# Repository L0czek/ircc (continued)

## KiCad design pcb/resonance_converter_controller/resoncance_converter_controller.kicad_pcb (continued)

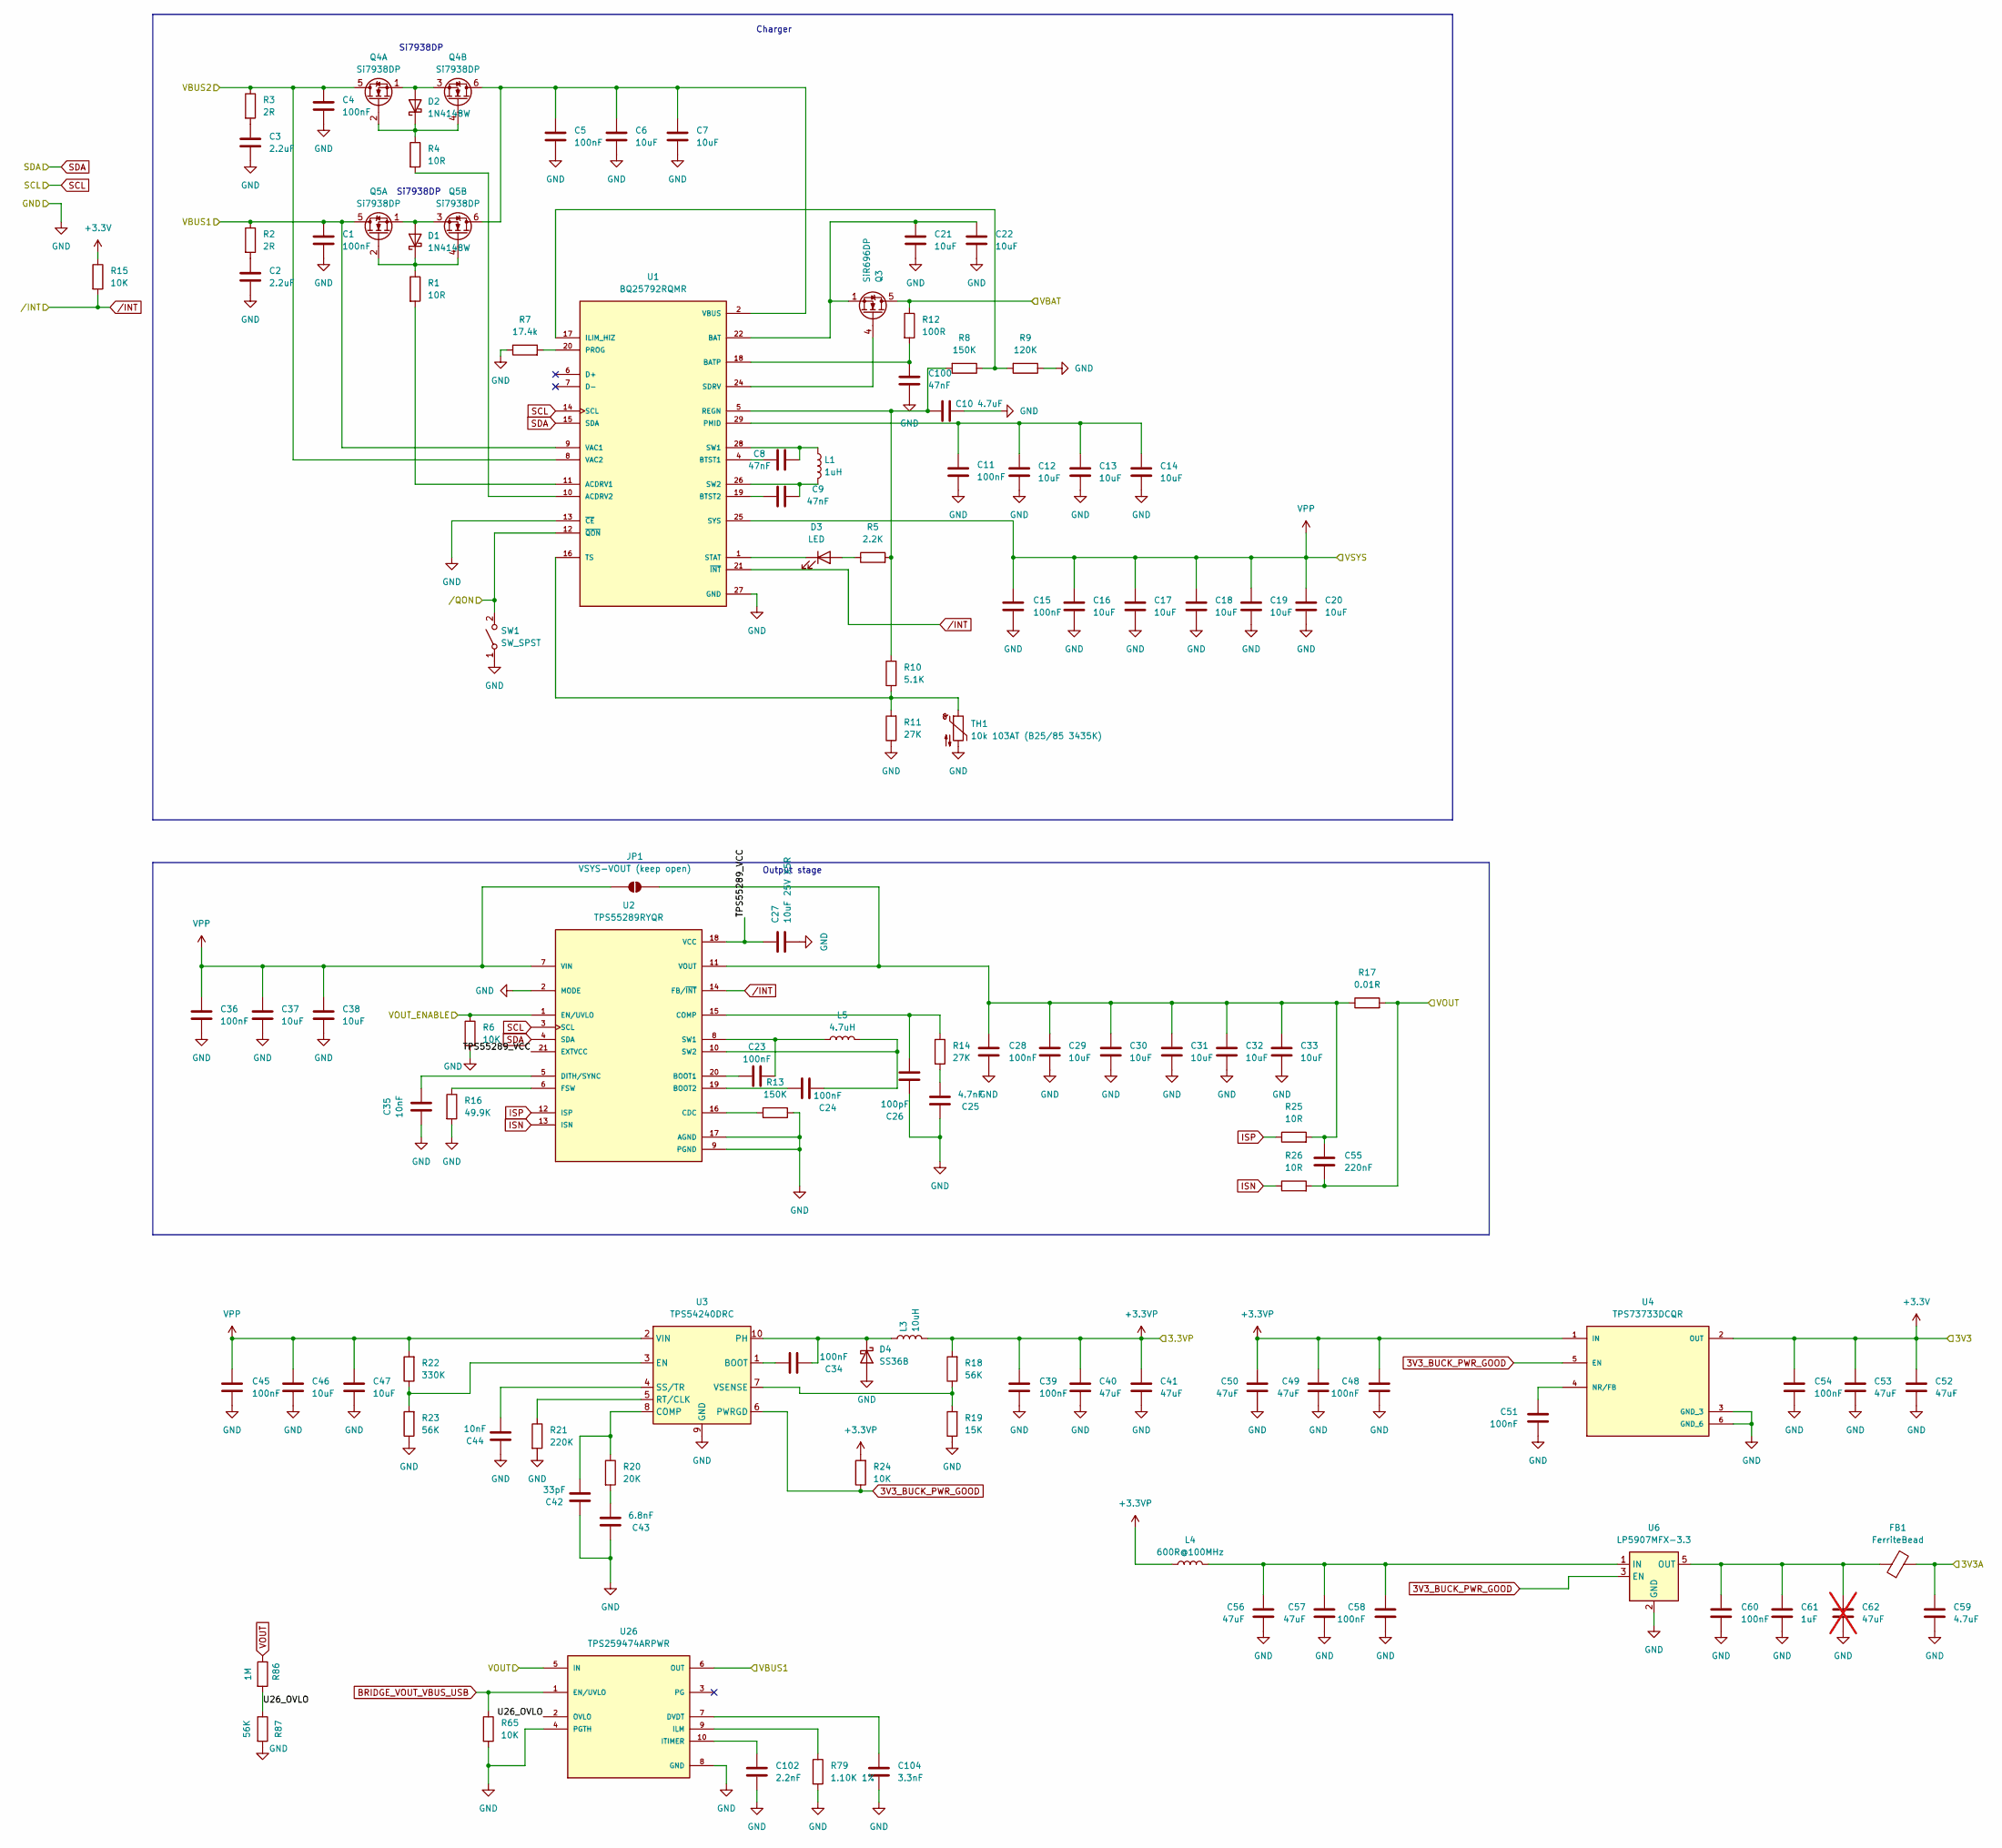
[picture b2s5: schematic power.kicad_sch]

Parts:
C1, C4, C5, C11, C15, C23, C24, C28, C34, C36, C39, C45, C48, C51, C54, C58, C60: 100nF; C_0402_1005Metric; LCSC C307331
C2, C3: 2.2uF; C_1206_3216Metric; LCSC C50254
C6, C7, C12, C13, C14, C16, C17, C18, C19, C20, C21, C22, C29, C30, C31, C32, C33, C37, C38, C46, C47: 10uF; C_1206_3216Metric; LCSC C13585
C8, C9, C100: 47nF; C_0402_1005Metric
C10: 4.7uF; C_1206_3216Metric; LCSC C29823
C25: 4.7nF; C_0402_1005Metric; LCSC C1538
C26: 100pF; C_0402_1005Metric; LCSC C1546
C27: 10uF 25V X5R; C_0805_2012Metric; LCSC C15850
C35, C44: 10nF; C_0402_1005Metric; LCSC C15195
C40, C41, C49, C50, C52, C53, C56, C57: 47uF; C_1206_3216Metric; LCSC C96123
C42: 33pF; C_0402_1005Metric; LCSC C1562
C43: 6.8nF; C_0402_1005Metric; LCSC C1542
C55: 220nF; C_0402_1005Metric; LCSC C16772
C59: 4.7uF; C_0805_2012Metric; LCSC C1779
C61: 1uF; C_0603_1608Metric; LCSC C15849
C62: 47uF; C_1206_3216Metric; LCSC C96123; not fitted
C102: 2.2nF; C_0402_1005Metric; LCSC C1531
C104: 3.3nF; C_0402_1005Metric; LCSC C26404
D1, D2: 1N4148W; D_SOD-123; LCSC C81598
D3: LED; LED_0805_2012Metric; LCSC C84256
D4: SS36B; D_SMB; LCSC C18199182
FB1: FerriteBead; L_0805_2012Metric; LCSC C1017
JP1: VSYS-VOUT (keep open); SolderJumper-2_P1.3mm_Open_RoundedPad1.0x1.5mm
L1: 1uH; L_10.4x10.4_H4.8
L3: 10uH; C_2220_5750Metric
L4: 600R@100MHz; L_0805_2012Metric; MPN GZ2012D601TF; LCSC C1017
L5: 4.7uH; MPEV1D1040L4R7; MPN MPEV1D1040L4R7
Q3: SiR696DP; PowerPAK_SO-8_Single
Q4, Q5: Si7938DP; PowerPAK_SO-8_Dual
R1, R4, R25, R26: 10R; R_0402_1005Metric; LCSC C25077
R2, R3: 2R; R_1206_3216Metric; LCSC C137316
R5: 2.2K; R_0402_1005Metric; LCSC C25879
R6, R15, R24, R65: 10K; R_0402_1005Metric; LCSC C25744
R7: 17.4k; R_0402_1005Metric; LCSC C26957
R8, R13: 150K; R_0402_1005Metric; LCSC C25755
R9: 120K; R_0402_1005Metric; LCSC C25750
R10: 5.1K; R_0402_1005Metric; LCSC C25905
R11, R14: 27K; R_0402_1005Metric; LCSC C25771
R12: 100R; R_0402_1005Metric; LCSC C25076
R16: 49.9K; R_0402_1005Metric; LCSC C25897
R17: 0.01R; R_1206_3216Metric; LCSC C188070
R18, R23, R87: 56K; R_0402_1005Metric; LCSC C25796
R19: 15K; R_0402_1005Metric; LCSC C25756
R20: 20K; R_0402_1005Metric; LCSC C25765
R21: 220K; R_0402_1005Metric; LCSC C25767
R22: 330K; R_0402_1005Metric; LCSC C25778
R79: 1.10K 1%; R_0402_1005Metric; LCSC C25860
R86: 1M; R_0402_1005Metric; LCSC C26083
SW1: SW_SPST; SW_SPST_EVQPE1
TH1: 10k 103AT (B25/85 3435K); R_0603_1608Metric; MPN NCP18XH103F03RB; LCSC C13564
U1: BQ25792RQMR; QFN40P400X400X100-29N; PARTREV 11/2019
U2: TPS55289RYQR; VREG_TPS55289RYQR; PARTREV August 2022
U3: TPS54240DRC; Texas_DRC0010J_ThermalVias
U4: TPS73733DCQR; IC_TPS73733DCQR; PARTREV R
U6: LP5907MFX-3.3; SOT-23-5
U26: TPS259474ARPWR; IC_TPS259474ARPWR; PARTREV A

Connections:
3V3_BUCK_PWR_GOOD: R24.1, U3.6 (PWRGD), U4.5 (EN), U6.3 (EN)
+3.3VP: C39.1, C40.1, C41.1, C48.1, C49.1, C50.1, L3.2, L4.1, R18.2, R24.2, U4.1 (IN); also elsewhere on the board
+BATT: Q3.5 (D), R12.1; also elsewhere on the board
/Controller/VOUT_ENABLE: R6.1, U2.1 (EN/UVLO); also elsewhere on the board
/Power supply/TPS55289_VCC: C27.1, U2.18 (VCC), U2.21 (EXTVCC)
/Power supply/U26_OVLO: R86.2, R87.1, U26.2 (OVLO)
BAT: C21.1, C22.1, Q3.1 (S), Q3.2 (S), Q3.3 (S), U1.22 (BAT), U1.23 (BAT)
BRIDGE_VOUT_VBUS_USB: R65.1, U26.1 (EN/UVLO); also elsewhere on the board
GND: C1.2, C2.2, C3.2, C4.2, C5.2, C6.2, C7.2, C10.2, C11.2, C12.2, C13.2, C14.2, C15.2, C16.2, C17.2, C18.2, C19.2, C20.2, C21.2, C22.2, C25.1, C26.1, C27.2, C28.2, C29.2, C30.2, C31.2, C32.2, C33.2, C35.1, C36.2, C37.2, C38.2, C39.2, C40.2, C41.2, C42.1, C43.1, C44.1, C45.2, C46.2, C47.2, C48.2, C49.2, C50.2, C51.2, C52.2, C53.2, C54.2, C56.2, C57.2, C58.2, C59.2, C60.2, C61.2, C62.2, C100.2, C102.2, C104.2, D4.2 (A), R6.2, R7.1, R9.1, R11.1, R13.1, R16.2, R19.1, R21.2, R23.1, R65.2, R79.2, R87.2, SW1.1 (A), TH1.2, U1.13 (~CE), U1.27 (GND), U2.2 (MODE), U2.9 (PGND), U2.17 (AGND), U3.9 (GND), U3.11 (GND), U4.3 (GND_3), U4.6 (GND_6), U6.2 (GND), U26.4 (PGTH), U26.8 (GND); also elsewhere on the board
INT_I2C_SCL: U1.14 (SCL), U2.3 (SCL); also elsewhere on the board
INT_I2C_SDA: U1.15 (SDA), U2.4 (SDA); also elsewhere on the board
ISN: R26.1, U2.13 (ISN)
ISP: R25.1, U2.12 (ISP)
unnamed: C2.1, R2.2
unnamed: C3.1, R3.2
unnamed: C25.2, R14.2
unnamed: C43.2, R20.2
unnamed: D1.2 (A), Q5.1 (S1), Q5.3 (S2)
unnamed: D1.1 (K), Q5.2 (G1), Q5.4 (G2), R1.1
unnamed: D2.2 (A), Q4.1 (S1), Q4.3 (S2)
unnamed: D2.1 (K), Q4.2 (G1), Q4.4 (G2), R4.1
unnamed: D3.2 (A), R5.1
unnamed: D3.1 (K), U1.1 (STAT)
unnamed: C34.1, D4.1 (K), L3.1, U3.10 (PH)
unnamed: C28.1, C29.1, C30.1, C31.1, C32.1, C33.1, C55.1, JP1.2 (B), R17.1, R25.2, U2.11 (VOUT)
unnamed: Q3.4 (G), U1.24 (SDRV)
unnamed: R1.2, U1.11 (ACDRV1)
unnamed: R4.2, U1.10 (ACDRV2)
unnamed: C100.1, R12.2, U1.18 (BATP)
unnamed: C8.1, U1.4 (BTST1)
unnamed: C9.1, U1.19 (BTST2)
unnamed: R8.1, R9.2, U1.17 (ILIM_HIZ)
unnamed: C11.1, C12.1, C13.1, C14.1, U1.29 (PMID)
unnamed: R7.2, U1.20 (PROG)
unnamed: C10.1, R5.2, R8.2, R10.2, U1.5 (REGN)
unnamed: C8.2, L1.1, U1.28 (SW1)
unnamed: C9.2, L1.2, U1.26 (SW2)
unnamed: R10.1, R11.2, TH1.1, U1.16 (TS)
unnamed: C23.1, U2.20 (BOOT1)
unnamed: C24.2, U2.19 (BOOT2)
unnamed: R13.2, U2.16 (CDC)
unnamed: C26.2, R14.1, U2.15 (COMP)
unnamed: C35.2, U2.5 (DITH/SYNC)
unnamed: R16.1, U2.6 (FSW)
unnamed: C23.2, L5.1, U2.8 (SW1)
unnamed: C24.1, L5.2, U2.10 (SW2)
unnamed: C34.2, U3.1 (BOOT)
unnamed: C42.2, R20.1, U3.8 (COMP)
unnamed: R22.1, R23.2, U3.3 (EN)
unnamed: R21.1, U3.5 (RT/CLK)
unnamed: C44.2, U3.4 (SS/TR)
unnamed: R18.1, R19.2, U3.7 (VSENSE)
unnamed: C51.1, U4.4 (NR/FB)
unnamed: C56.1, C57.1, C58.1, L4.2, U6.1 (IN)
unnamed: C60.1, C61.1, C62.1, FB1.1, U6.5 (OUT)
unnamed: C104.1, U26.7 (DVDT)
unnamed: R79.1, U26.9 (ILM)
unnamed: C102.1, U26.10 (ITIMER)
VAA: C59.1, FB1.2; also elsewhere on the board
VBUS: C5.1, C6.1, C7.1, Q4.6 (D2), Q5.6 (D2), U1.2 (VBUS), U1.3 (VBUS)
VBUS_DOCK: C4.1, Q4.5 (D1), R3.1, U1.8 (VAC2); also elsewhere on the board
VBUS_USBC: C1.1, Q5.5 (D1), R2.1, U1.9 (VAC1), U26.6 (OUT); also elsewhere on the board
VCC: C52.1, C53.1, C54.1, R15.1, U4.2 (OUT); also elsewhere on the board
VOUT: C55.2, R17.2, R26.2, R86.1, U26.5 (IN); also elsewhere on the board
VSYS: C15.1, C16.1, C17.1, C18.1, C19.1, C20.1, C36.1, C37.1, C38.1, C45.1, C46.1, C47.1, JP1.1 (A), R22.2, U1.25 (SYS), U2.7 (VIN), U3.2 (VIN); also elsewhere on the board
/INT: R15.2, U1.21 (~INT), U2.14 (FB/~INT); also elsewhere on the board
/QON: SW1.2 (B), U1.12 (~QON); also elsewhere on the board

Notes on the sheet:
Output stage
Si7938DP
Charger

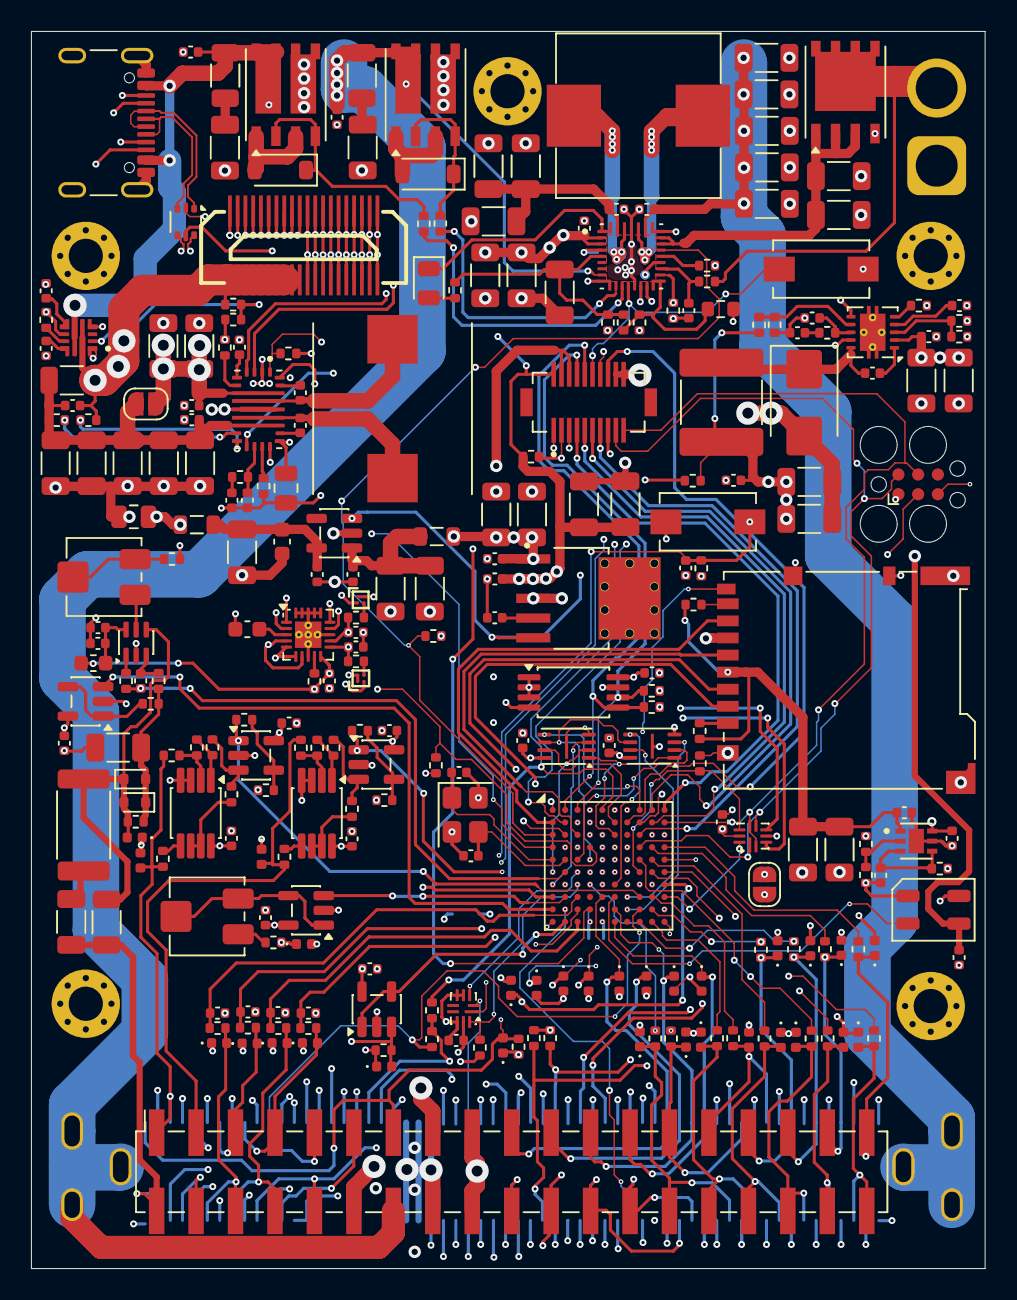
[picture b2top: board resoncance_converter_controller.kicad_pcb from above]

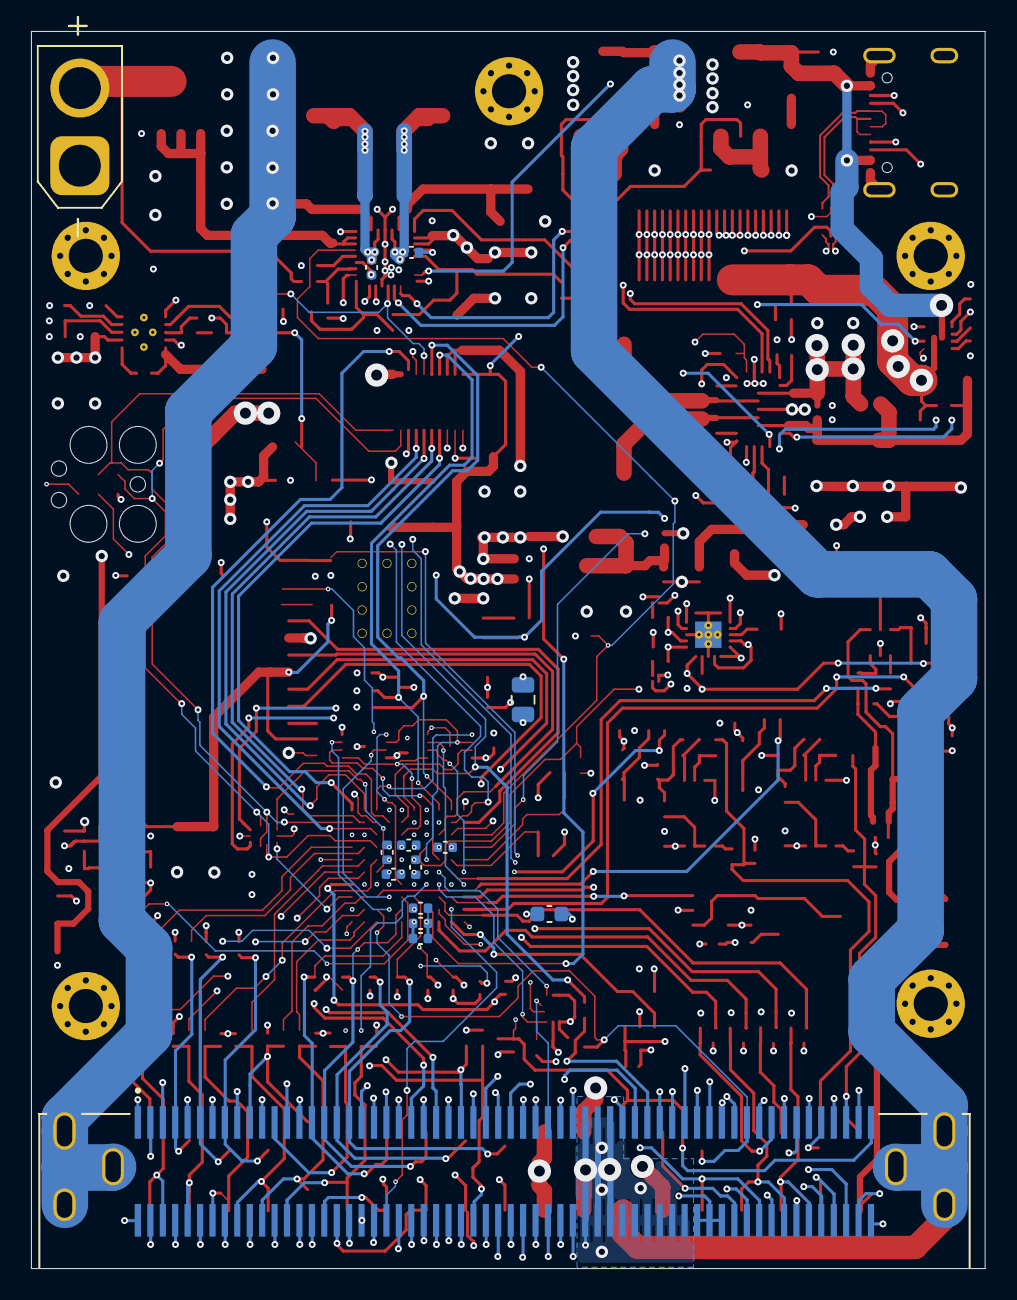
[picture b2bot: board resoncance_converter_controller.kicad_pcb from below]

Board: 6 copper layers, 61.4 x 79.7 mm, 289 parts (14 on the bottom side), 210 nets.

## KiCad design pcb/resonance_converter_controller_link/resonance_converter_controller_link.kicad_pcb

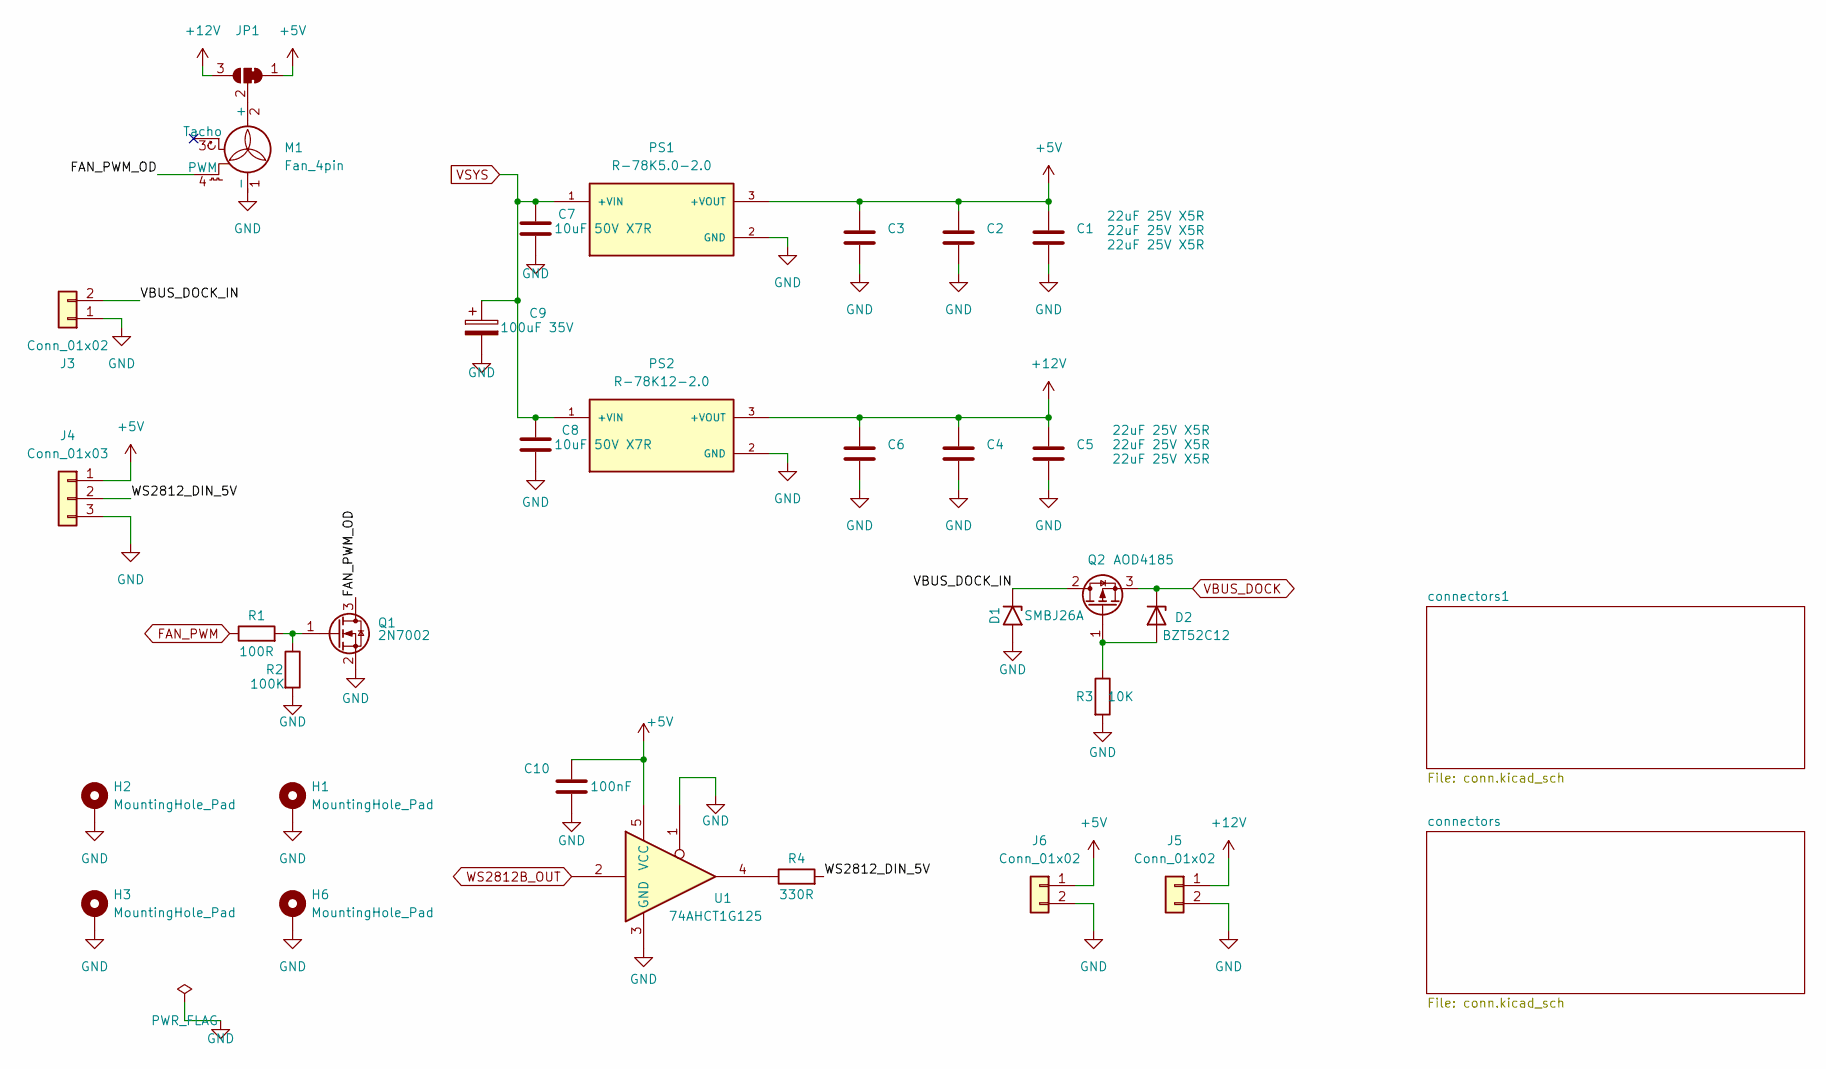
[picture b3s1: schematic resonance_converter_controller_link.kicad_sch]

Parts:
C1, C2, C3, C4, C5, C6: 22uF 25V X5R; C_1206_3216Metric; LCSC Part C12891
C7, C8: 10uF 50V X7R; C_1210_3225Metric
C9: 100uF 35V; CP_Elec_8x10
C10: 100nF; C_0402_1005Metric; LCSC Part C307331
D1: SMBJ26A; D_SMB; MPN SMBJ26A; LCSC Part C19077580
D2: BZT52C12; D_SOD-123; MPN BZT52C12; LCSC Part C19077410
H1, H2, H3, H6: MountingHole_Pad; MountingHole_2.2mm_M2_Pad_Via
J3: Conn_01x02; PhoenixContact_MC_1,5_2-GF-5.08_1x02_P5.08mm_Horizontal_Thr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
J4: Conn_01x03; PinHeader_1x03_P2.54mm_Horizontal
J5, J6: Conn_01x02; PhoenixContact_MC_1,5_2-G-5.08_1x02_P5.08mm_Horizontal
JP1: SolderJumper_3_Bridged12; SolderJumper-3_P1.3mm_Bridged12_RoundedPad1.0x1.5mm
M1: Fan_4pin; FanPinHeader_1x04_P2.54mm_Vertical
PS1: R-78K5.0-2.0; CONV_R-78K5.0-2.0; MPN R-78K5.0-2.0
PS2: R-78K12-2.0; CONV_R-78K12-2.0; MPN R-78K12-2.0
Q1: 2N7002; SOT-23; MPN 2N7002; LCSC Part C8545
Q2: AOD4185; TO-252-2; MPN AOD4185; LCSC Part C400894
R1: 100R; R_0402_1005Metric; LCSC Part C25076
R2: 100K; R_0402_1005Metric; LCSC Part C25741
R3: 10K; R_0402_1005Metric; LCSC Part C25744
R4: 330R; R_0402_1005Metric; LCSC Part C25104
U1: 74AHCT1G125; SOT-23-5; MPN 74AHCT1G125GV; LCSC Part C52140417

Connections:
+5V: C1.1, C2.1, C3.1, C10.1, J4.1, J6.1, JP1.1 (A), PS1.3 (+VOUT), U1.5 (VCC)
+12V: C4.1, C5.1, C6.1, J5.1, JP1.3 (B), PS2.3 (+VOUT)
/FAN_PWM_OD: M1.4 (PWM), Q1.3 (D)
/VBUS_DOCK_IN: D1.1 (A1), J3.2, Q2.2 (D)
/WS2812_DIN_5V: J4.2, R4.2
FAN_PWM: R1.1; also elsewhere on the board
GND: C1.2, C2.2, C3.2, C4.2, C5.2, C6.2, C7.2, C8.2, C9.2, C10.2, D1.2 (A2), H1.1 (1_1), H2.1 (1_1), H3.1 (1_1), H6.1 (1_1), J3.1, J4.3, J5.2, J6.2, M1.1 (-), PS1.2 (GND), PS2.2 (GND), Q1.2 (S), R2.2, R3.2, U1.1, U1.3 (GND); also elsewhere on the board
unnamed: D2.2 (A), Q2.1 (G), R3.1
unnamed: JP1.2 (C), M1.2 (+)
unnamed: Q1.1 (G), R1.2, R2.1
unnamed: R4.1, U1.4
VBUS_DOCK: D2.1 (K), Q2.3 (S); also elsewhere on the board
VSYS: C7.1, C8.1, C9.1, PS1.1 (+VIN), PS2.1 (+VIN); also elsewhere on the board
WS2812B_OUT: U1.2; also elsewhere on the board

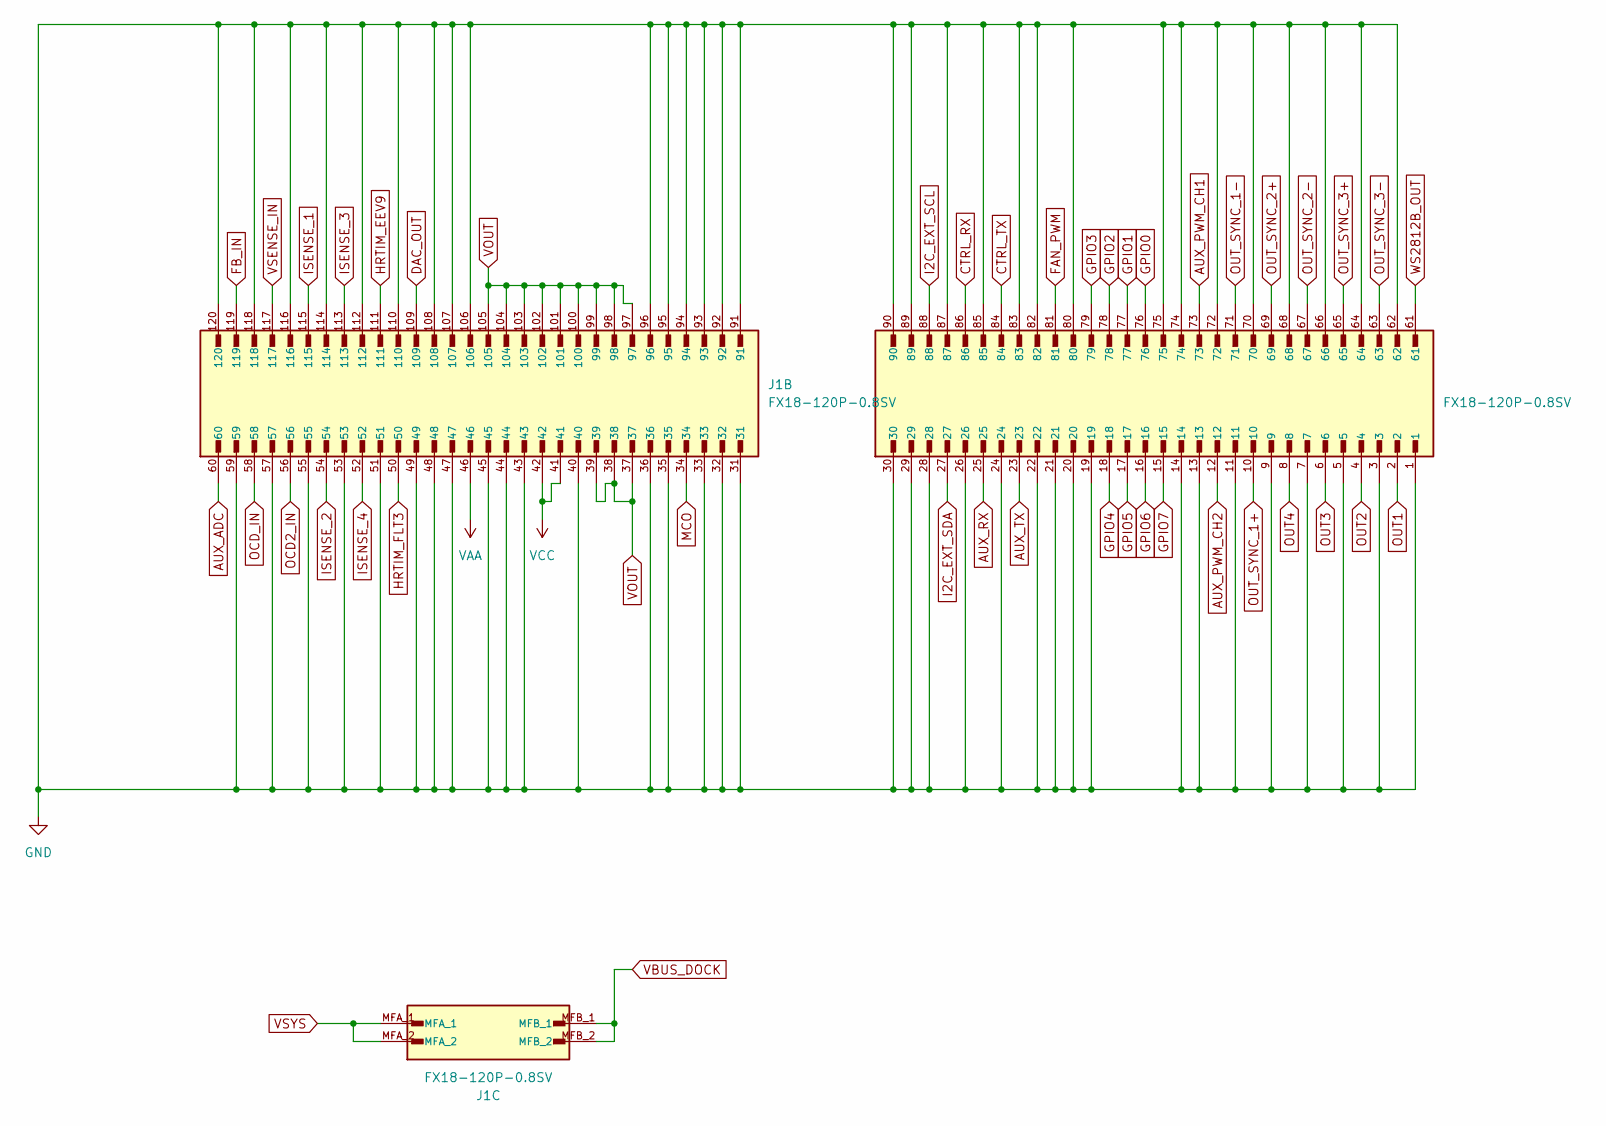
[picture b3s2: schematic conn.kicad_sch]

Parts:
J1: FX18-120P-0.8SV; HIROSE_FX18-120P-0.8SV; PARTREV 11.07.21

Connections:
AUX_ADC: J1.60; also elsewhere on the board
AUX_PWM_CH1: J1.73; also elsewhere on the board
AUX_PWM_CH2: J1.12; also elsewhere on the board
AUX_RX: J1.25; also elsewhere on the board
AUX_TX: J1.23; also elsewhere on the board
CTRL_RX: J1.86; also elsewhere on the board
CTRL_TX: J1.84; also elsewhere on the board
DAC_OUT: J1.109; also elsewhere on the board
FAN_PWM: J1.81; also elsewhere on the board
FB_IN: J1.119; also elsewhere on the board
GND: J1.1, J1.3, J1.5, J1.7, J1.9, J1.11, J1.13, J1.14, J1.19, J1.20, J1.21, J1.22, J1.24, J1.26, J1.28, J1.29, J1.30, J1.31, J1.32, J1.33, J1.35, J1.36, J1.40, J1.43, J1.44, J1.45, J1.47, J1.48, J1.49, J1.51, J1.53, J1.55, J1.57, J1.59, J1.62, J1.64, J1.66, J1.68, J1.70, J1.72, J1.74, J1.75, J1.80, J1.82, J1.83, J1.85, J1.87, J1.89, J1.90, J1.91, J1.92, J1.93, J1.94, J1.95, J1.96, J1.106, J1.107, J1.108, J1.110, J1.112, J1.114, J1.116, J1.118, J1.120; also elsewhere on the board
GPIO0: J1.76; also elsewhere on the board
GPIO1: J1.77; also elsewhere on the board
GPIO2: J1.78; also elsewhere on the board
GPIO3: J1.79; also elsewhere on the board
GPIO4: J1.18; also elsewhere on the board
GPIO5: J1.17; also elsewhere on the board
GPIO6: J1.16; also elsewhere on the board
GPIO7: J1.15; also elsewhere on the board
HRTIM_EEV9: J1.111; also elsewhere on the board
HRTIM_FLT3: J1.50; also elsewhere on the board
I2C_EXT_SCL: J1.88; also elsewhere on the board
I2C_EXT_SDA: J1.27; also elsewhere on the board
ISENSE_1: J1.115; also elsewhere on the board
ISENSE_2: J1.54; also elsewhere on the board
ISENSE_3: J1.113; also elsewhere on the board
ISENSE_4: J1.52; also elsewhere on the board
MCO: J1.34; also elsewhere on the board
OCD2_IN: J1.56; also elsewhere on the board
OCD_IN: J1.58; also elsewhere on the board
OUT1: J1.2; also elsewhere on the board
OUT2: J1.4; also elsewhere on the board
OUT3: J1.6; also elsewhere on the board
OUT4: J1.8; also elsewhere on the board
OUT_SYNC_1+: J1.10; also elsewhere on the board
OUT_SYNC_1-: J1.71; also elsewhere on the board
OUT_SYNC_2+: J1.69; also elsewhere on the board
OUT_SYNC_2-: J1.67; also elsewhere on the board
OUT_SYNC_3+: J1.65; also elsewhere on the board
OUT_SYNC_3-: J1.63; also elsewhere on the board
VAA: J1.46; also elsewhere on the board
VBUS_DOCK: J1.MFB_1, J1.MFB_2; also elsewhere on the board
VCC: J1.41, J1.42; also elsewhere on the board
VOUT: J1.37, J1.38, J1.39, J1.97, J1.98, J1.99, J1.100, J1.101, J1.102, J1.103, J1.104, J1.105; also elsewhere on the board
VSENSE_IN: J1.117; also elsewhere on the board
VSYS: J1.MFA_1, J1.MFA_2; also elsewhere on the board
WS2812B_OUT: J1.61; also elsewhere on the board

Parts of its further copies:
J2: FX18-120P-0.8SV; HIROSE_FX18-120P-0.8SV; PARTREV 11.07.21

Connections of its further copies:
AUX_ADC: J2.60; also elsewhere on the board
AUX_PWM_CH1: J2.73; also elsewhere on the board
AUX_PWM_CH2: J2.12; also elsewhere on the board
AUX_RX: J2.25; also elsewhere on the board
AUX_TX: J2.23; also elsewhere on the board
CTRL_RX: J2.86; also elsewhere on the board
CTRL_TX: J2.84; also elsewhere on the board
DAC_OUT: J2.109; also elsewhere on the board
FAN_PWM: J2.81; also elsewhere on the board
FB_IN: J2.119; also elsewhere on the board
GND: J2.1, J2.3, J2.5, J2.7, J2.9, J2.11, J2.13, J2.14, J2.19, J2.20, J2.21, J2.22, J2.24, J2.26, J2.28, J2.29, J2.30, J2.31, J2.32, J2.33, J2.35, J2.36, J2.40, J2.43, J2.44, J2.45, J2.47, J2.48, J2.49, J2.51, J2.53, J2.55, J2.57, J2.59, J2.62, J2.64, J2.66, J2.68, J2.70, J2.72, J2.74, J2.75, J2.80, J2.82, J2.83, J2.85, J2.87, J2.89, J2.90, J2.91, J2.92, J2.93, J2.94, J2.95, J2.96, J2.106, J2.107, J2.108, J2.110, J2.112, J2.114, J2.116, J2.118, J2.120; also elsewhere on the board
GPIO0: J2.76; also elsewhere on the board
GPIO1: J2.77; also elsewhere on the board
GPIO2: J2.78; also elsewhere on the board
GPIO3: J2.79; also elsewhere on the board
GPIO4: J2.18; also elsewhere on the board
GPIO5: J2.17; also elsewhere on the board
GPIO6: J2.16; also elsewhere on the board
GPIO7: J2.15; also elsewhere on the board
HRTIM_EEV9: J2.111; also elsewhere on the board
HRTIM_FLT3: J2.50; also elsewhere on the board
I2C_EXT_SCL: J2.88; also elsewhere on the board
I2C_EXT_SDA: J2.27; also elsewhere on the board
ISENSE_1: J2.115; also elsewhere on the board
ISENSE_2: J2.54; also elsewhere on the board
ISENSE_3: J2.113; also elsewhere on the board
ISENSE_4: J2.52; also elsewhere on the board
MCO: J2.34; also elsewhere on the board
OCD2_IN: J2.56; also elsewhere on the board
OCD_IN: J2.58; also elsewhere on the board
OUT1: J2.2; also elsewhere on the board
OUT2: J2.4; also elsewhere on the board
OUT3: J2.6; also elsewhere on the board
OUT4: J2.8; also elsewhere on the board
OUT_SYNC_1+: J2.10; also elsewhere on the board
OUT_SYNC_1-: J2.71; also elsewhere on the board
OUT_SYNC_2+: J2.69; also elsewhere on the board
OUT_SYNC_2-: J2.67; also elsewhere on the board
OUT_SYNC_3+: J2.65; also elsewhere on the board
OUT_SYNC_3-: J2.63; also elsewhere on the board
VAA: J2.46; also elsewhere on the board
VBUS_DOCK: J2.MFB_1, J2.MFB_2; also elsewhere on the board
VCC: J2.41, J2.42; also elsewhere on the board
VOUT: J2.37, J2.38, J2.39, J2.97, J2.98, J2.99, J2.100, J2.101, J2.102, J2.103, J2.104, J2.105; also elsewhere on the board
VSENSE_IN: J2.117; also elsewhere on the board
VSYS: J2.MFA_1, J2.MFA_2; also elsewhere on the board
WS2812B_OUT: J2.61; also elsewhere on the board

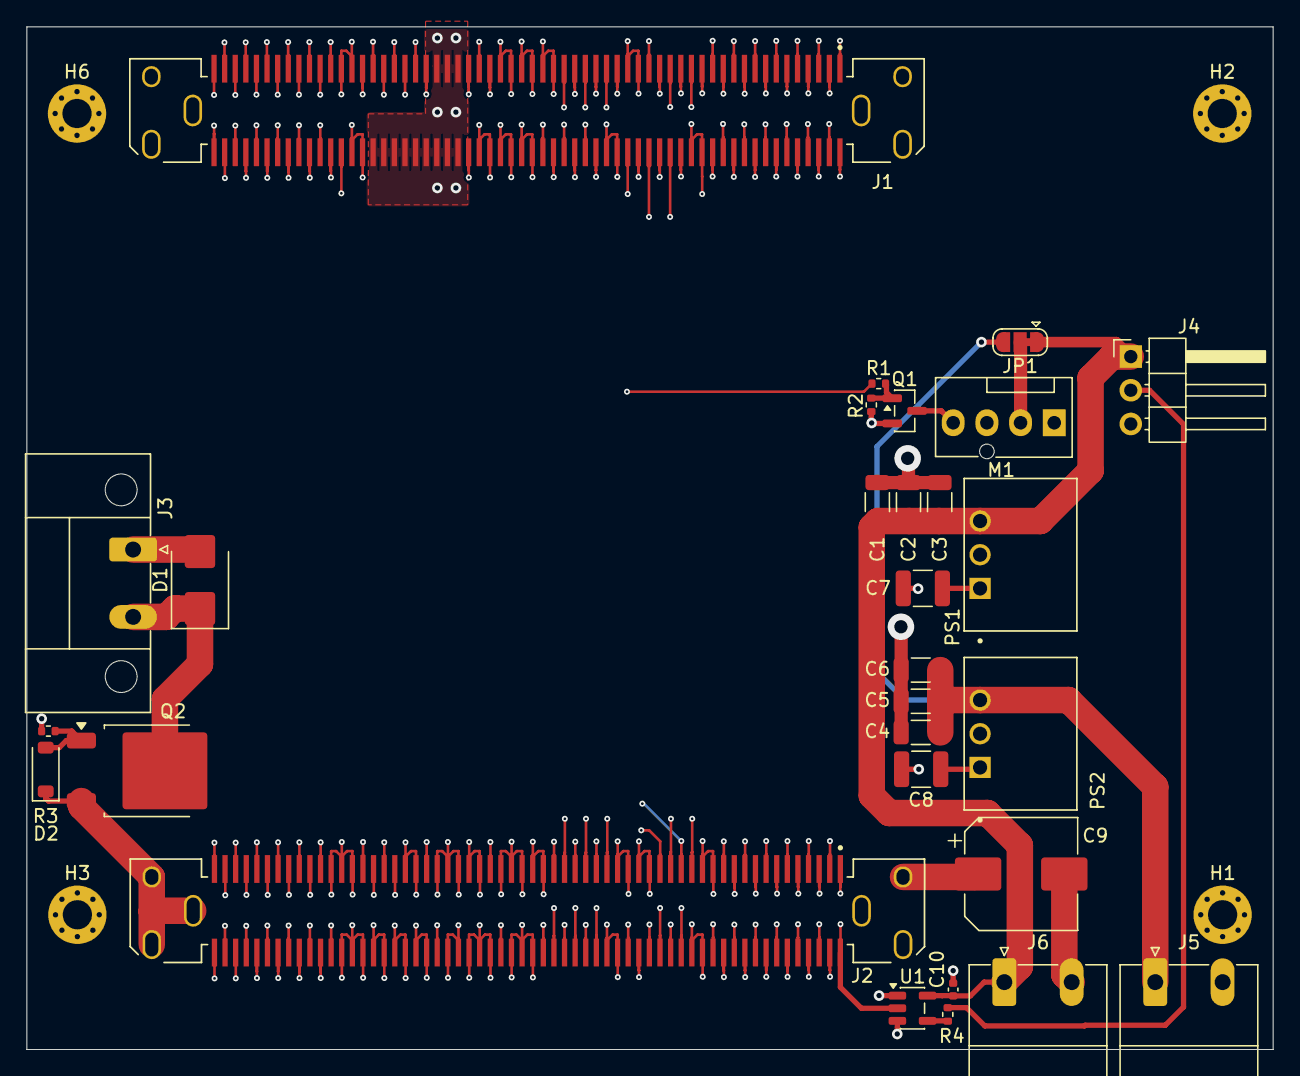
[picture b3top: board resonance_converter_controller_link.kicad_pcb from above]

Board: 6 copper layers, 94.0 x 77.1 mm, 33 parts (0 on the bottom side), 56 nets.
